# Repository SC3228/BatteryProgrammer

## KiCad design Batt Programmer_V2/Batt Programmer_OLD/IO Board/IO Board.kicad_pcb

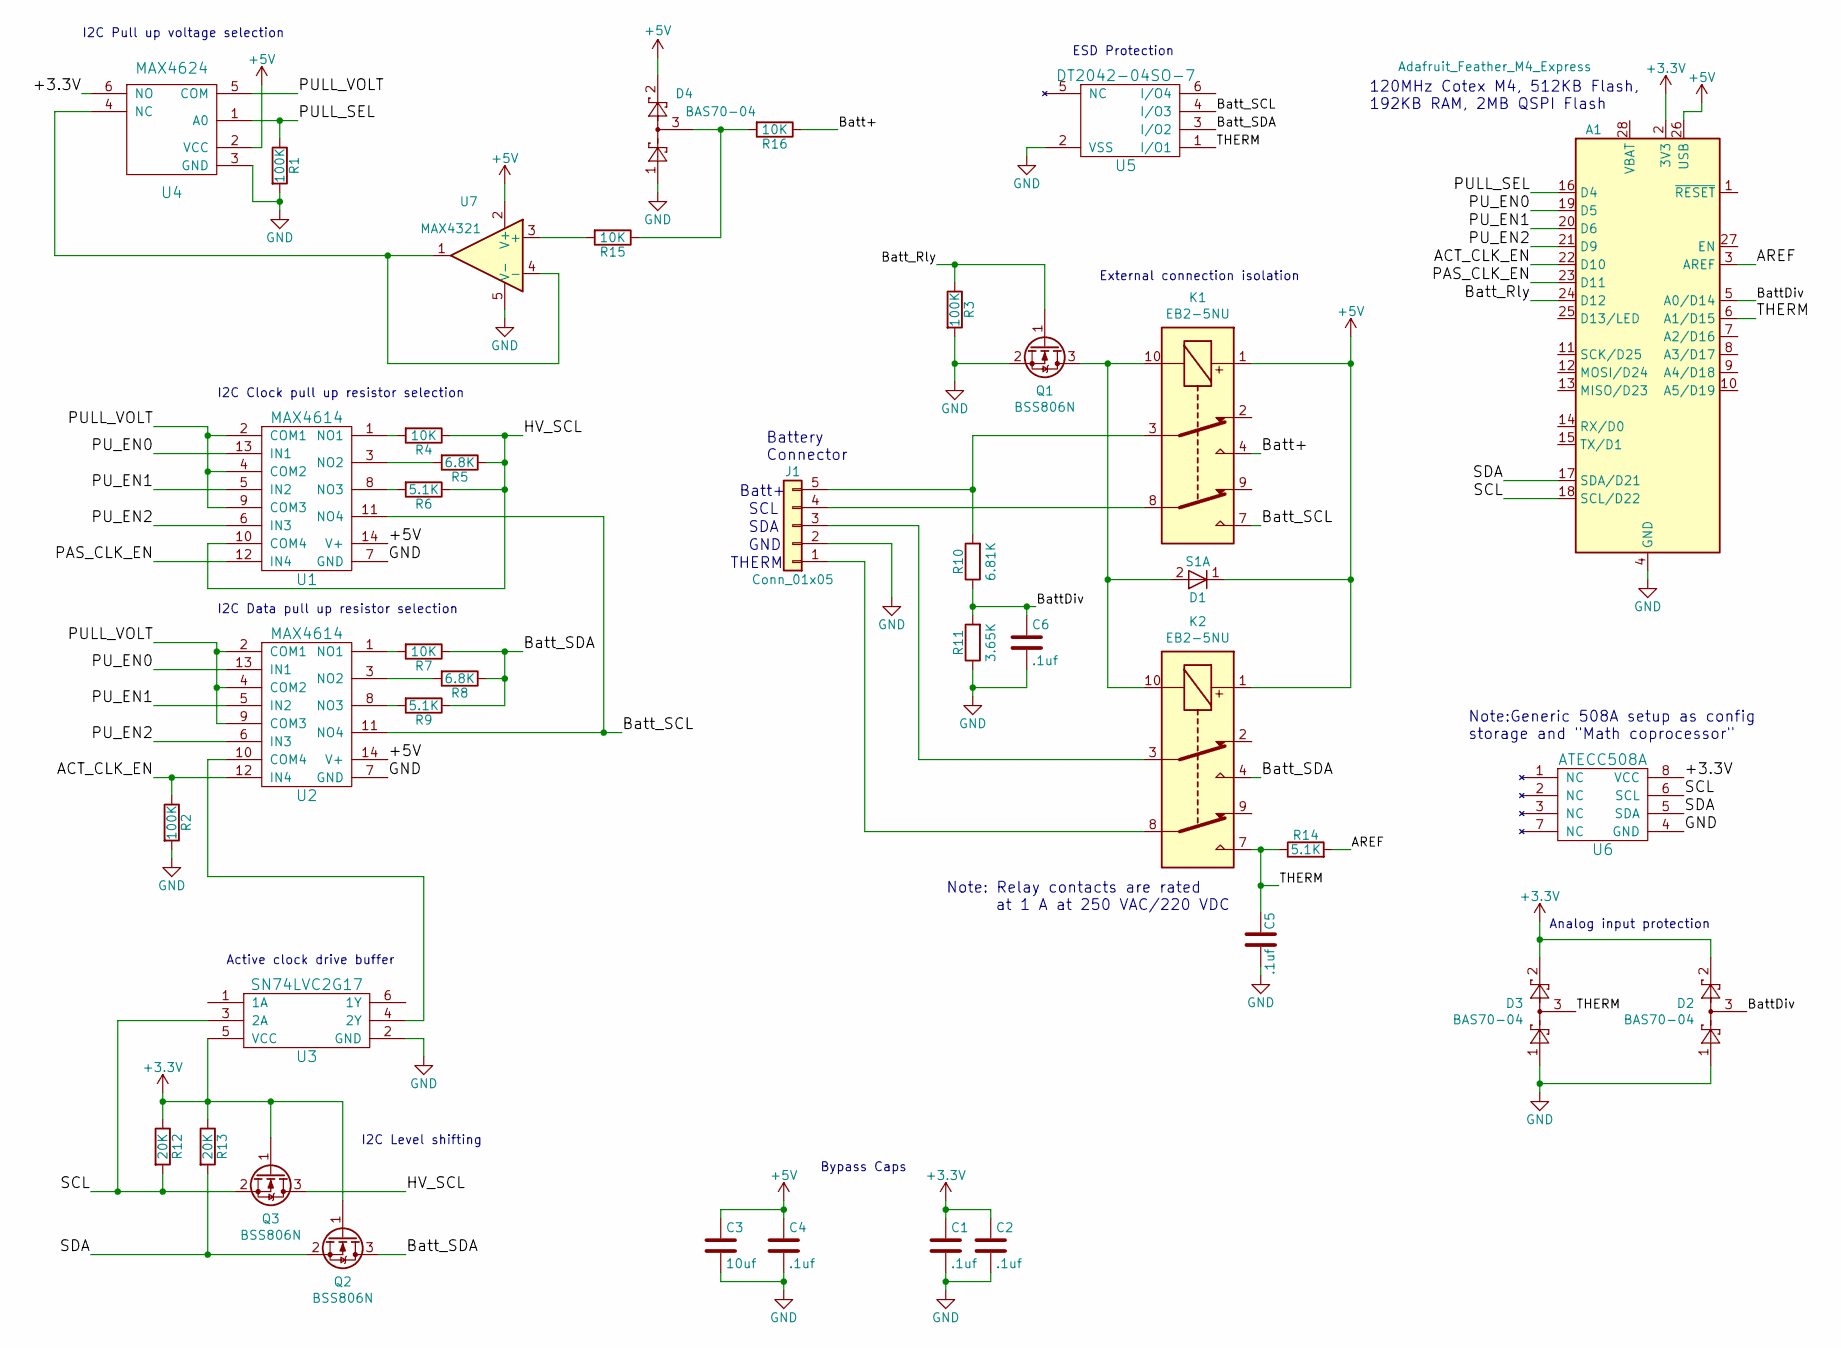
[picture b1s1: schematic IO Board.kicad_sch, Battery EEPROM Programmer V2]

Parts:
A1: Adafruit_Feather_M4_Express; Adafruit_Feather
C1, C2, C4, C5, C6: .1uf; C_1206_3216Metric_Pad1.33x1.80mm_HandSolder
C3: 10uf; C_1206_3216Metric_Pad1.33x1.80mm_HandSolder
D1: S1A; D_SMA_Handsoldering
D2, D3, D4: BAS70-04; SOT-23_Handsoldering
J1: Conn_01x05; PinHeader_1x05_P2.54mm_Vertical
K1, K2: EB2-5NU; Relay_DPDT_Omron_G6H-2F
Q1, Q2, Q3: BSS806N; SOT-23_Handsoldering
R1, R2, R3: 100K; R_1206_3216Metric_Pad1.30x1.75mm_HandSolder
R4, R7, R15, R16: 10K; R_1206_3216Metric_Pad1.30x1.75mm_HandSolder
R5, R8: 6.8K; R_1206_3216Metric_Pad1.30x1.75mm_HandSolder
R6, R9, R14: 5.1K; R_1206_3216Metric_Pad1.30x1.75mm_HandSolder
R10: 6.81K; R_1206_3216Metric_Pad1.30x1.75mm_HandSolder
R11: 3.65K; R_1206_3216Metric_Pad1.30x1.75mm_HandSolder
R12, R13: 20K; R_1206_3216Metric_Pad1.30x1.75mm_HandSolder
U1, U2: MAX4614; SOIC-14_3.9x8.7mm_P1.27mm
U3: SN74LVC2G17; SOT-23-6_Handsoldering
U4: MAX4624; SOT-23-6_Handsoldering
U5: DT2042-04SO-7; SOT-23-6_Handsoldering
U6: ATECC508A; SOIC-8_3.9x4.9mm_P1.27mm
U7: MAX4321; SOT-23-5_HandSoldering

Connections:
+3.3V: A1.2 (3V3), C1.1, C2.1, D2.2, D3.2, Q2.1 (G), Q3.1 (G), R12.1, R13.1, U3.5 (VCC), U4.6 (NO), U6.8 (VCC)
+5V: A1.26 (USB), C3.1, C4.1, D1.1 (C), D4.2, K1.1, K2.1, U1.14 (V+), U2.14 (V+), U4.2 (VCC), U7.2 (V+)
/ACT_CLK_EN: A1.22 (D10), R2.1, U2.12 (IN4)
/AREF: A1.3 (AREF), R14.2
/Batt+: K1.4, R16.1
/BattDiv: A1.5 (A0/D14), C6.1, D2.3, R10.1, R11.2
/Batt_Rly: A1.24 (D12), Q1.1 (G), R3.1
/Batt_SCL: K1.7, U1.11 (NO4), U2.11 (NO4), U5.4 (I/O3)
/Batt_SDA: K2.4, Q2.3 (D), R7.1, R8.1, R9.1, U5.3 (I/O2)
/HV_SCL: Q3.3 (D), R4.1, R5.1, R6.1, U1.10 (COM4)
/PAS_CLK_EN: A1.23 (D11), U1.12 (IN4)
/PULL_SEL: A1.16 (D4), R1.1, U4.1 (A0)
/PULL_VOLT: U1.2 (COM1), U1.4 (COM2), U1.9 (COM3), U2.2 (COM1), U2.4 (COM2), U2.9 (COM3), U4.5 (COM)
/PU_EN0: A1.19 (D5), U1.13 (IN1), U2.13 (IN1)
/PU_EN1: A1.20 (D6), U1.5 (IN2), U2.5 (IN2)
/PU_EN2: A1.21 (D9), U1.6 (IN3), U2.6 (IN3)
/SCL: A1.18 (SCL/D22), Q3.2 (S), R12.2, U3.3 (2A), U6.6 (SCL)
/SDA: A1.17 (SDA/D21), Q2.2 (S), R13.2, U6.5 (SDA)
/THERM: A1.6 (A1/D15), C5.1, D3.3, K2.7, R14.1, U5.1 (I/O1)
GND: A1.4 (GND), C1.2, C2.2, C3.2, C4.2, C5.2, C6.2, D2.1, D3.1, D4.1, J1.2, Q1.2 (S), R1.2, R2.2, R3.2, R11.1, U1.7 (GND), U2.7 (GND), U3.2 (GND), U4.3 (GND), U5.2 (VSS), U6.4 (GND), U7.5 (V-)
unnamed: D1.2 (A), K1.10, K2.10, Q1.3 (D)
unnamed: D4.3, R15.1, R16.2
unnamed: J1.1, K2.8
unnamed: J1.3, K2.3
unnamed: J1.4, K1.8
unnamed: J1.5, K1.3, R10.2
unnamed: R4.2, U1.1 (NO1)
unnamed: R5.2, U1.3 (NO2)
unnamed: R6.2, U1.8 (NO3)
unnamed: R7.2, U2.1 (NO1)
unnamed: R8.2, U2.3 (NO2)
unnamed: R9.2, U2.8 (NO3)
unnamed: R15.2, U7.3 (+)
unnamed: U2.10 (COM4), U3.4 (2Y)
unnamed: U4.4 (NC), U7.1, U7.4 (-)

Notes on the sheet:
External connection isolation
Batt+
SDA
Battery Connector
I2C Level shifting
I2C Clock pull up resistor selection
Note:Generic 508A setup as config storage and "Math coprocessor"
I2C Data pull up resistor selection
Note: Relay contacts are rated at 1 A at 250 VAC/220 VDC
Analog input protection
SCL
ESD Protection
Active clock drive buffer
120MHz Cotex M4, 512KB Flash, 192KB RAM, 2MB QSPI Flash
I2C Pull up voltage selection
Bypass Caps
GND
THERM

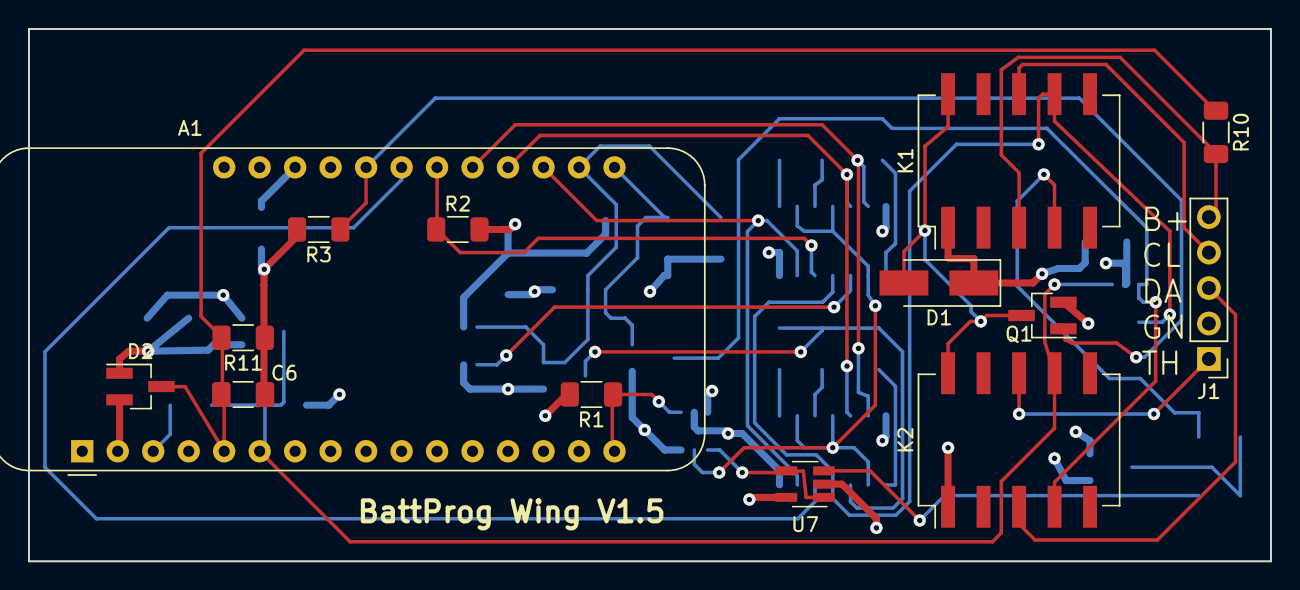
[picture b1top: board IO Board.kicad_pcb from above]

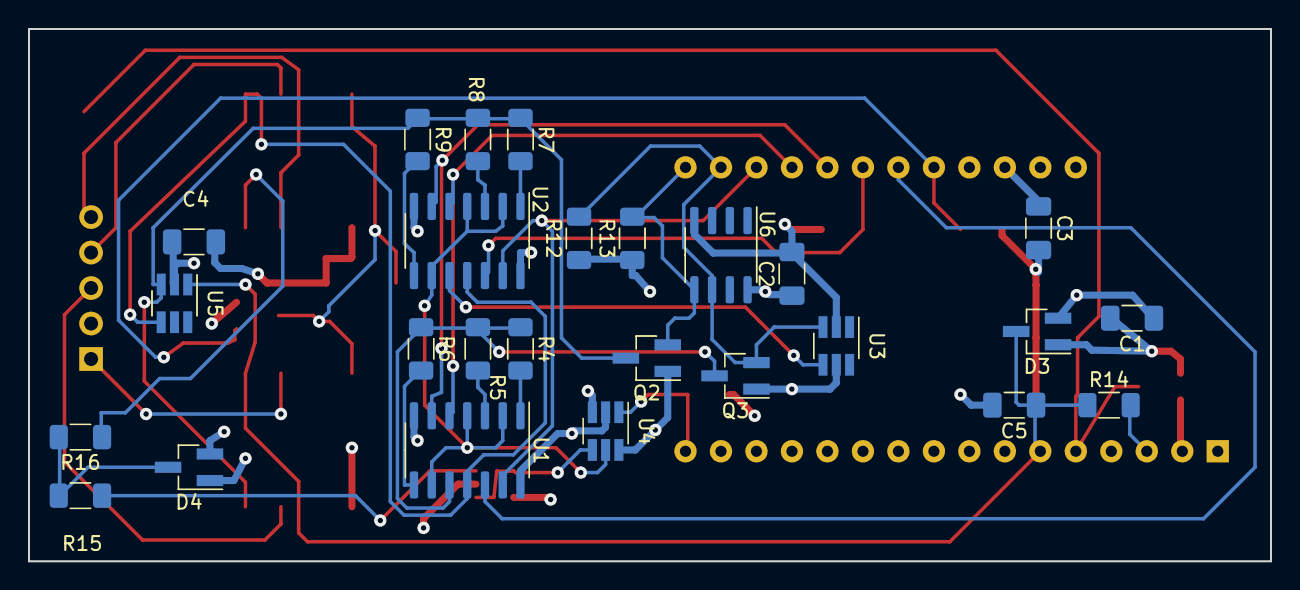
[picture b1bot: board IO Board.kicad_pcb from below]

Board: 4 copper layers, 88.9 x 38.1 mm, 40 parts (26 on the bottom side), 35 nets.

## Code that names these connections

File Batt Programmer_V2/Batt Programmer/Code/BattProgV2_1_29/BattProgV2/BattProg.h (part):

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#define RELAY_CTRL	12	// Relay control pin, high activates relays
#define I2C_CLK		22	// I2C clock pin

#define PULL_SEL	4	// Pull up voltage select line, 0 = VBatt, 1 = 3.3V

#define PU_EN0		5	// Enable for 10K pullup, active high
#define PU_EN1		6	// Enable for 6.8K pullup, active high
#define PU_EN2		9	// Enable for 5.1K pullup, active high
#define PAS_CLK_EN	11	// SCL enable for passive clock drive, active high
#define ACT_CLK_EN	10	// SCL enable for active clock drive, active high

#define BATT_PLUS	A0	// Analog input to read battery voltage
#define THERM		A1	// Analog input for thermistor

// Pullup voltage selects
#define PULLUP_V3p3		0	// 3.3 Volts
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
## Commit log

2024-01-31 Added All Local Files from Steve PC
